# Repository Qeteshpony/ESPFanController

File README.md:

# ESPFanController

[Hardware Documentation](https://qeteshpony.github.io/ESPFanController)

Controller for up to three 5V or 12V PWM-Fans with an ESP32 at it's core 

The included yaml file is my config for ESP-Home but of course this can also be programmed in any compatible language you like...

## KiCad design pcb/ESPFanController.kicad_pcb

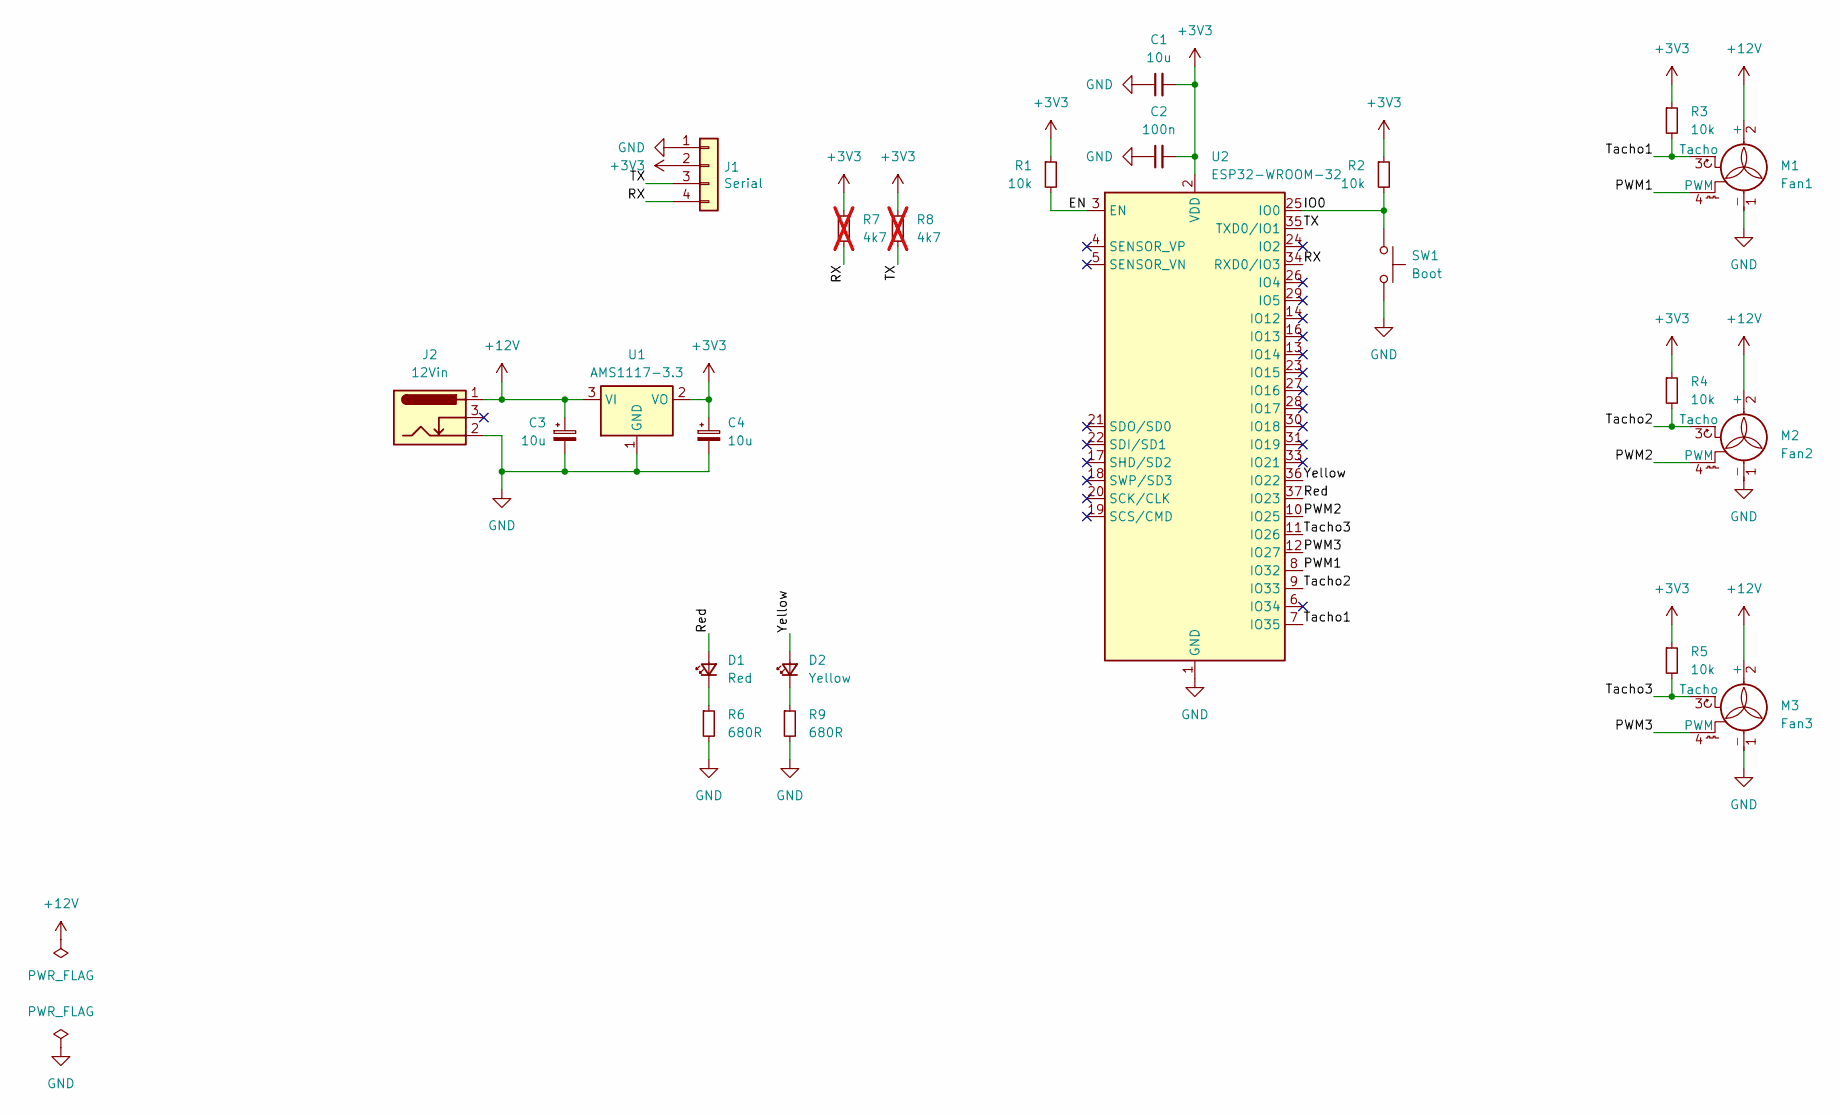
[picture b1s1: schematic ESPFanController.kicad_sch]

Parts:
C1: 10u; C_0402_1005Metric; LCSC C15525
C2: 100n; C_0402_1005Metric; LCSC C1525
C3, C4: 10u; CP_EIA-3216-18_Kemet-A; LCSC C7171
D1: Red; LED_0603_1608Metric; LCSC C2286
D2: Yellow; LED_0603_1608Metric; LCSC C72038
J1: Serial; JST_PH_B4B-PH-K_1x04_P2.00mm_Vertical; LCSC C131334
J2: 12Vin; BarrelJack_Horizontal
M1: Fan1; FanPinHeader_1x04_P2.54mm_Vertical
M2: Fan2; FanPinHeader_1x04_P2.54mm_Vertical
M3: Fan3; FanPinHeader_1x04_P2.54mm_Vertical
R1, R2, R3, R4, R5: 10k; R_0402_1005Metric; LCSC C25744
R6, R9: 680R; R_0402_1005Metric; LCSC C25130
R7, R8: 4k7; R_0402_1005Metric_Pad0.72x0.64mm_HandSolder; LCSC C25900; not fitted
SW1: Boot; SW_Push_1P1T_XKB_TS-1187A; LCSC C318884
U1: AMS1117-3.3; SOT-223-3_TabPin2; LCSC C6186
U2: ESP32-WROOM-32; LCSC C701341

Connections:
+3V3: C1.2, C2.2, C4.1, J1.2, R1.1, R2.1, R3.1, R4.1, R5.1, R7.1, R8.1, U1.2 (VO), U2.2 (VDD)
+12V: C3.1, J2.1, M1.2 (+), M2.2 (+), M3.2 (+), U1.3 (VI)
/EN: R1.2, U2.3 (EN)
/IO0: R2.2, SW1.2, U2.25 (IO0)
/PWM1: M1.4 (PWM), U2.8 (IO32)
/PWM2: M2.4 (PWM), U2.10 (IO25)
/PWM3: M3.4 (PWM), U2.12 (IO27)
/RX: J1.4, R7.2, U2.34 (RXD0/IO3)
/Red: D1.2 (A), U2.37 (IO23)
/TX: J1.3, R8.2, U2.35 (TXD0/IO1)
/Tacho1: M1.3 (Tacho), R3.2, U2.7 (IO35)
/Tacho2: M2.3 (Tacho), R4.2, U2.9 (IO33)
/Tacho3: M3.3 (Tacho), R5.2, U2.11 (IO26)
/Yellow: D2.2 (A), U2.36 (IO22)
GND: C1.1, C2.1, C3.2, C4.2, J1.1, J2.2, M1.1 (-), M2.1 (-), M3.1 (-), R6.2, R9.2, SW1.1, U1.1 (GND), U2.1 (GND), U2.15 (GND), U2.38 (GND), U2.39 (GND)
unnamed: D1.1 (K), R6.1
unnamed: D2.1 (K), R9.1

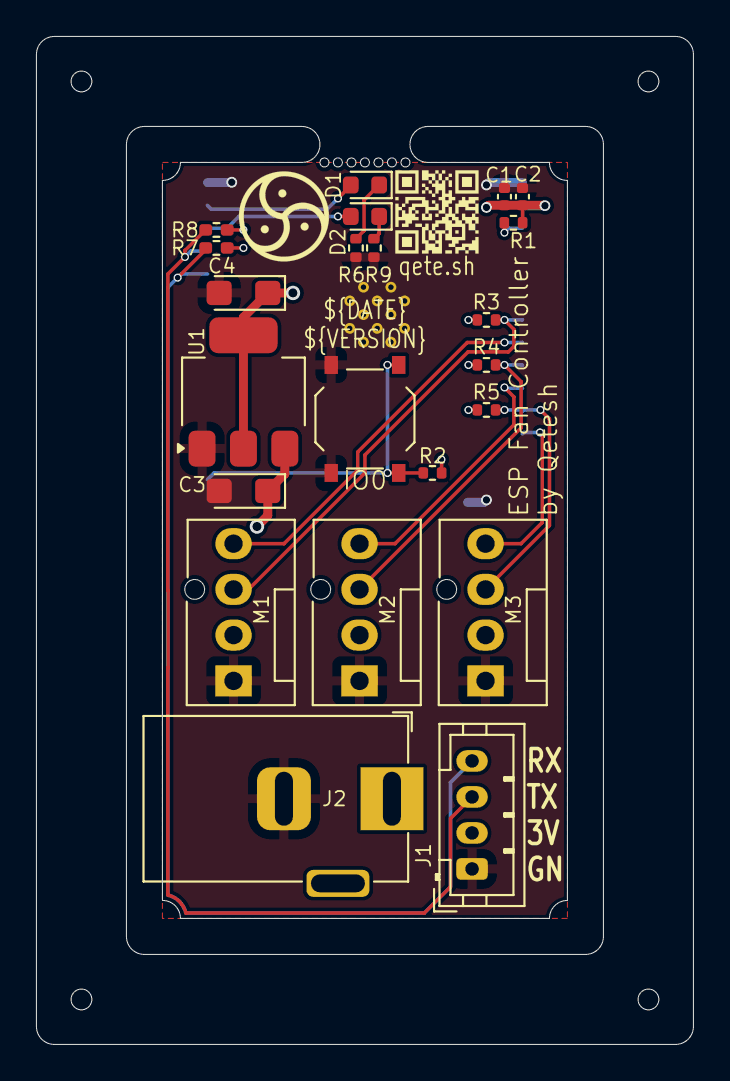
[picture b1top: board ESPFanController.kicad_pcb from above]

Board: 2 copper layers, 36.5 x 56.0 mm, 24 parts (1 on the bottom side), 17 nets.

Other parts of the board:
mouse-bite-2mm-slot: VAL**; mouse-bite-2x5mm-slot-onesided-v2

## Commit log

2024-09-20 feat: initial commit
2024-09-20 feat: add position for pullups
2024-09-20 feat: add edge rails
2024-09-29 feat: add second LED
    feat: add cutouts to the corners
    feat: add optional pull-ups to serial pins
    for I2C use after programming
2024-09-29 feat: add ESP-Home code
2024-09-29 docs: update README
2024-09-29 chore(main): release 1.0.0
2024-09-29 test: add DRC Exclusions
2024-10-12 ci: update kibot config
2024-10-12 docs: add bottom view
2024-10-16 feat: ESPHome example code
2024-10-16 chore(main): release 1.1.0
